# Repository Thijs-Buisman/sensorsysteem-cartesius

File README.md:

# Sensorsysteem – Wijk Cartesius, Utrecht

> Automatisch passantentelsysteem op basis van een lasersensor met fotodiode.  
> Ontwikkeld in het kader van het QUEST-project **"Gezond leven in Cartesius"** – Hogeschool Utrecht, 2026.

---

## Wat doet dit systeem?

Dit systeem telt automatisch hoeveel voetgangers, fietsers en auto's er door een doorgang in de wijk Cartesius (Utrecht) passeren. De data wordt lokaal opgeslagen op een SD-kaart als CSV-bestand, voorzien van een tijdstempel via een RTC-module.

Het systeem bestaat uit twee onderdelen:
- **Zender** – een lasermodule die een onzichtbare laserstraal uitzendt
- **Ontvanger** – een fotodiode die registreert wanneer de laserstraal wordt onderbroken

Wanneer iemand de straal onderbreekt, classificeert het systeem de passage als voetganger, fietser of auto op basis van de duur en het patroon van de onderbreking.

---

## Resultaten veldtest (21 mei 2026)

| Gebruikerstype | Sensor | Handmatig | Afwijking |
|----------------|--------|-----------|-----------|
| Voetganger     | 50     | 47        | 6,4%      |
| Fietser        | 28     | 32        | 12,5%     |
| Auto           | 3      | 0         | –         |
| **Totaal**     | **81** | **79**    | **2,5%**  |

Totale afwijking: **2,5%** — ruim binnen de gestelde eis van maximaal 15%.

---

## Inhoud van deze repository

```
sensorsysteem-cartesius/
│
├── code/
│   ├── Sensor_code_V3.ino       # Definitieve sensorcode (gebruik deze)
│   └── Sensor_code_V2.ino       # Vorige versie, ter referentie
│
├── kicad/
│   ├── PCB_sensor/              # KiCad 9.0 project – sensorprintplaat (ontvanger)
│   └── PCB_laser/               # KiCad 9.0 project – laserprintplaat (zender)
│
├── 3d-ontwerp/                    # STL-bestanden en .itp autodesk inventor van alle 7 behuizingsonderdelen
│
├── testdata/
│   ├── 05201342.CSV        # Ruwe sensordata van de veldtest
│   └── Sensor_validatie_test.xlsx     # Vergelijking sensor vs. handmatige telling
│
└── docs/
    ├── Overdracht_Sensorsysteem_Cartesius.pdf   # Overdrachts document (begin hier)
    ├── Handleiding_Sensorprototype.pdf
    ├── Proof_of_Concept_Sensorsysteem.pdf
    └── PCB-ontwerp_sensor_V1.pdf
```

---

## Benodigde hardware

| Component | Type | Kosten (ca.) |
|-----------|------|-------------|
| Microcontroller | Arduino Nano | €4,00 |
| Lasermodule | KY-008 | €1,50 |
| Fotodiode | SGPD5051C6 | €3,50 |
| RTC-module | DS3231 | €4,00 |
| SD-kaartmodule | standaard SPI | €2,50 |
| Protoboard + bedrading | – | €5,00 |
| 3D-print materiaal | PLA, 573 gram | €12,00 |
| Powerbanks (2x) | 5V USB | €20,00 |
| **Totaal** | | **~€83,92** |

---

## Benodigde software

- [Arduino IDE](https://www.arduino.cc/en/software) – voor de sensorcode
- [KiCad 9.0](https://www.kicad.org/) – voor de PCB-schema's en layouts
- [PrusaSlicer](https://www.prusa3d.com/page/prusaslicer_424/) of [Cura](https://ultimaker.com/software/ultimaker-cura/) – voor de 3D-print bestanden
- [Autodesk Inventor](https://www.autodesk.com/nl/products/inventor/overview) - 3D-modelleringssoftware voor ontwerpers en ingenieurs

---

## Snel aan de slag

1. Download of clone deze repository
2. Open `docs/Overdrachts_document_Sensorsysteem_Cartesius.docx` — dit is het startpunt
3. Upload `code/Sensor_code_V3.ino` via Arduino IDE naar een Arduino Nano
4. Volg de plaatsingsinstructies in `docs/Handleiding_Sensorprototype.docx`

---

## Project & opleiding

| | |
|---|---|
| **Project** | Gezond leven in Cartesius |
| **Opdrachtgever** | Hanneke Kruize – Lectoraat Building Future Cities (RAAK PRO) |
| **Opleiding** | GCL/IDE · QUEST 30EC · Hogeschool Utrecht |
| **Auteur** | Thijs Buisman · Studentnummer 1855662 |
| **Groep** | Groep 8 (Boas Janssen, Joost, Kim, Melisa, Stef, Thijs Buisman) |
| **Docentcoach** | Marit Béguin |
| **Jaar** | 2025–2026 |

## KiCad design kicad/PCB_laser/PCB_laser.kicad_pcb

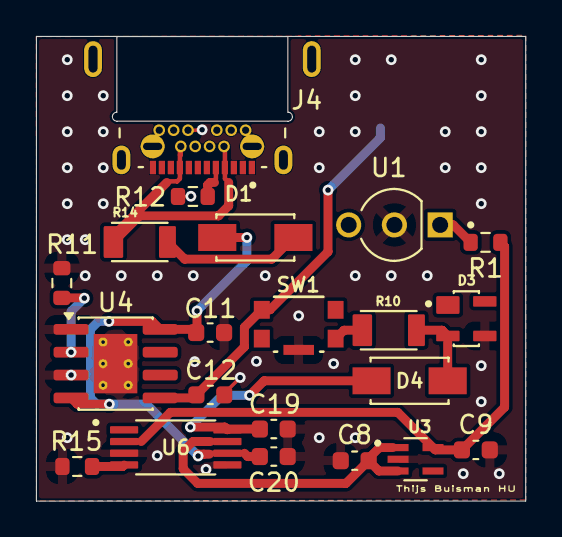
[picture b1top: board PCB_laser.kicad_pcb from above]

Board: 2 copper layers, 27.2 x 25.8 mm, 22 parts (1 on the bottom side), 14 nets.

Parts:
C8, C9, C19, C20: 1uF; C_0603_1608Metric
C11, C12: 10uF; C_0603_1608Metric
D1, D4: SS14; DIOM4325X250N
D3: SP0503BAHTG; SOT143
J4: SS-52400-004; STEWART_SS-52400-004
J7: Conn_01x02; PinSocket_1x02_P2.54mm_Vertical_SMD_Pin1Right
R1: 56; R_0603_1608Metric
R10, R14: NANOSMDC016F-2; RESC3115X65N
R11: 1.2K; R_0603_1608Metric
R12: 5.1K; R_0603_1608Metric
R15: 10K; R_0603_1608Metric
SW1: KMR211GLFS; KMR2XXG_CNK
U1: D6505I; LED_SSL-LX3059IGW-CA
U3: MIC5365-3.3YC5-TR; SOT65P210X110-5N
U4: TP4056-42-ESOP8; SOIC-8-1EP_3.9x4.9mm_P1.27mm_EP2.41x3.3mm_ThermalVias
U6: TPS2115APW; SOP65P640X120-8N

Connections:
+3V3: C9.2, R1.1, U3.5 (VOUT), U6.2 (D0)
Batterij beschermd: C19.2, D4.C, U6.8 (1N1)
GND: C8.1, C9.1, C11.1, C12.2, C19.1, C20.1, D3.3, J4.B5 (CC2), J7.2, R11.2, R12.2, R15.1, SW1.5, U1.2 (COM), U3.2 (GND), U4.1 (TEMP), U4.3 (GND), U4.9 (EPAD), U6.3 (D1), U6.5 (GND)
unnamed: D1.A, R14.2
unnamed: D3.2, D4.A, R10.2
unnamed: J4.A5 (CC1), R12.1
unnamed: R10.1, SW1.4
unnamed: R1.2, U1.1 (LD-A)
unnamed: R11.1, U4.2 (PROG)
unnamed: R15.2, U6.4 (ILIM)
VBUS: J4.A4 (VBUS_A), J4.A9 (VBUS_A), J4.B4 (VBUS_B), J4.B9 (VBUS_B), R14.1
VBUS beschermd: C11.2, C20.2, D1.C, U4.4 (V_{CC}), U4.8 (CE), U6.6 (1N2)
VIN_SYS: C8.2, U3.1 (VIN), U3.3 (EN), U6.7 (OUT)
batterij+: C12.1, J7.1, SW1.1, U4.5 (BAT)

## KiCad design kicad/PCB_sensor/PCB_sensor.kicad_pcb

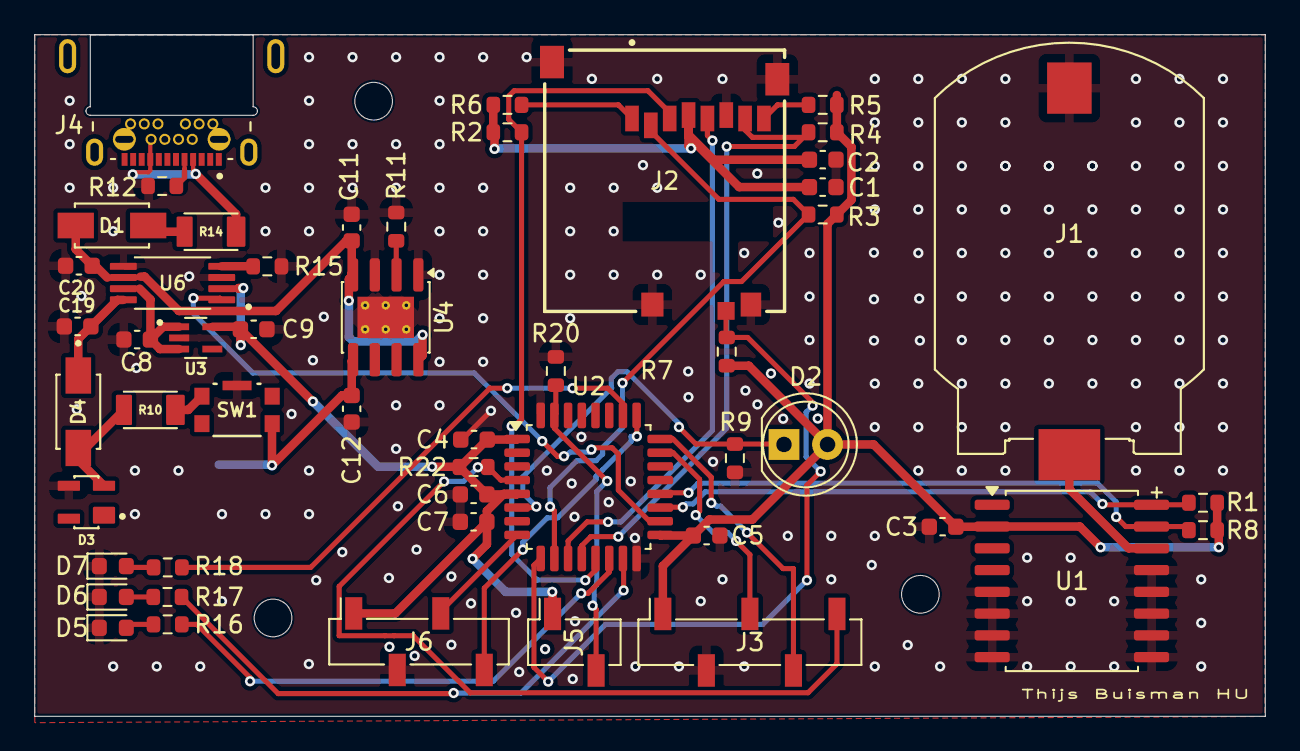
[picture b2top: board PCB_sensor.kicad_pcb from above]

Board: 2 copper layers, 71.8 x 39.8 mm, 52 parts (1 on the bottom side), 37 nets.

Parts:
C1, C3, C4, C5, C6: 100nF; C_0603_1608Metric
C2, C7, C11, C12: 10uF; C_0603_1608Metric
C8, C9, C19, C20: 1uF; C_0603_1608Metric
D1, D4: SS14; DIOM4325X250N
D2: LED_D5.0mm
D3: SP0503BAHTG; SOT143
D5, D6, D7: LED; LED_0603_1608Metric
J1: S8421-45R; HARWIN_S8421-45R
J2: MEM2052-00-195-00-A_REVA; GCT_MEM2052-00-195-00-A_REVA
J3: Conn_01x05; PinSocket_1x05_P2.54mm_Vertical_SMD_Pin1Right
J4: SS-52400-004; STEWART_SS-52400-004
J5, J7: Conn_01x02; PinSocket_1x02_P2.54mm_Vertical_SMD_Pin1Right
J6: Conn_01x04; PinSocket_1x04_P2.54mm_Vertical_SMD_Pin1Right
R1, R8: 4.7K; R_0603_1608Metric
R2, R3, R4, R5, R6, R7: 10k; R_0603_1608Metric
R9, R15, R20, R22: 10K; R_0603_1608Metric
R10, R14: NANOSMDC016F-2; RESC3115X65N
R11: 1.2K; R_0603_1608Metric
R12: 5.1K; R_0603_1608Metric
R16, R17, R18: 330; R_0603_1608Metric
SW1: KMR211GLFS; KMR2XXG_CNK
U1: DS3231M; SOIC-16W_7.5x10.3mm_P1.27mm
U2: STM32L010K8Tx; LQFP-32_7x7mm_P0.8mm
U3: MIC5365-3.3YC5-TR; SOT65P210X110-5N
U4: TP4056-42-ESOP8; SOIC-8-1EP_3.9x4.9mm_P1.27mm_EP2.41x3.3mm_ThermalVias
U6: TPS2115APW; SOP65P640X120-8N

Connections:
+3V3: C1.1, C2.1, C3.2, C4.2, C5.2, C6.2, C7.2, C9.2, D2.2 (Cathode_(-)), J2.P4 (VDD), J3.1, J5.1, J6.1, R1.1, R2.1, R3.1, R4.1, R5.1, R6.1, R7.1, R8.1, R22.2, U1.2 (VCC), U2.1 (VDD), U2.5 (VDDA), U2.17 (VDD), U3.5 (VOUT), U6.2 (D0)
ADC: D2.1 (Anode_(+)), R9.1, U2.6 (PA0)
BOOT0: J5.2, R20.2, U2.31 (BOOT0)
Batterij beschermd: C19.2, D4.C, U6.8 (1N1)
Blauwe LED: R18.1, U2.26 (PB3)
CS: J2.P2 (CD/DAT3), R3.2, U2.10 (PA4)
GND: C1.2, C2.2, C3.1, C4.1, C5.1, C6.1, C7.1, C8.1, C9.1, C11.1, C12.2, C19.1, C20.1, D3.3, D5.1 (K), D6.1 (K), D7.1 (K), J1.N, J2.G1 (SHIELD_GND), J2.G2 (SHIELD_GND), J2.G3 (SHIELD_GND), J2.G4 (SHIELD_GND), J2.P6 (VSS), J3.2, J4.B5 (CC2), J6.2, J7.2, R9.2, R11.2, R12.2, R15.1, R20.1, SW1.5, U1.5 (GND), U1.6 (GND), U1.7 (GND), U1.8 (GND), U1.9 (GND), U1.10 (GND), U1.11 (GND), U1.12 (GND), U1.13 (GND), U2.16 (VSS), U2.32 (VSS), U3.2 (GND), U4.1 (TEMP), U4.3 (GND), U4.9 (EPAD), U6.3 (D1), U6.5 (GND)
Groene LED: R17.1, U2.15 (PB1)
MISO: J2.P7 (DAT0), R4.2, U2.12 (PA6)
MOSI: J2.P3 (CMD), R2.2, U2.13 (PA7)
unnamed: D1.A, R14.2
unnamed: D3.2, D4.A, R10.2
unnamed: D5.2 (A), R16.2
unnamed: D6.2 (A), R17.2
unnamed: D7.2 (A), R18.2
unnamed: J2.P8 (DAT1), R5.2
unnamed: J2.P1 (DAT2), R6.2
unnamed: J4.A5 (CC1), R12.1
unnamed: R10.1, SW1.4
unnamed: J1.P, U1.14 (VBAT)
unnamed: R11.1, U4.2 (PROG)
unnamed: R15.2, U6.4 (ILIM)
PWR_SRC_STAT: U2.18 (PA8), U6.1 (STAT)
Reset: J3.5, R22.1, U2.4 (NRST)
Rode LED: R16.1, U2.14 (PB0)
SCK: J2.P5 (CLK), U2.11 (PA5)
SCL: R1.2, U1.16 (SCL), U2.19 (PA9)
SDA: R8.2, U1.15 (SDA), U2.20 (PA10)
SDCARD: J2.P9 (CD_PIN), R7.2, U2.9 (PA3)
SWCLK: J3.4, U2.24 (PA14)
SWDIO: J3.3, U2.23 (PA13)
USART1 RX: J6.4, U2.25 (PA15)
USART1 TX: J6.3, U2.8 (PA2)
VBUS: J4.A4 (VBUS_A), J4.A9 (VBUS_A), J4.B4 (VBUS_B), J4.B9 (VBUS_B), R14.1
VBUS beschermd: C11.2, C20.2, D1.C, U4.4 (V_{CC}), U4.8 (CE), U6.6 (1N2)
VIN_SYS: C8.2, U3.1 (VIN), U3.3 (EN), U6.7 (OUT)
batterij+: C12.1, J7.1, SW1.1, U4.5 (BAT)

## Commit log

2026-06-05 Revise README for clarity and accuracy
    Updated file names and descriptions in the README.

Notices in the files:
parts and their libraries:
COPYRIGHT: Copyright (C) 2023 Ultra Librarian. All rights reserved.
